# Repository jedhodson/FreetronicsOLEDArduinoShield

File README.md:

FreetronicsOLEDArduinoShield
============================

An Arduino shield for the Freetronics OLED Display

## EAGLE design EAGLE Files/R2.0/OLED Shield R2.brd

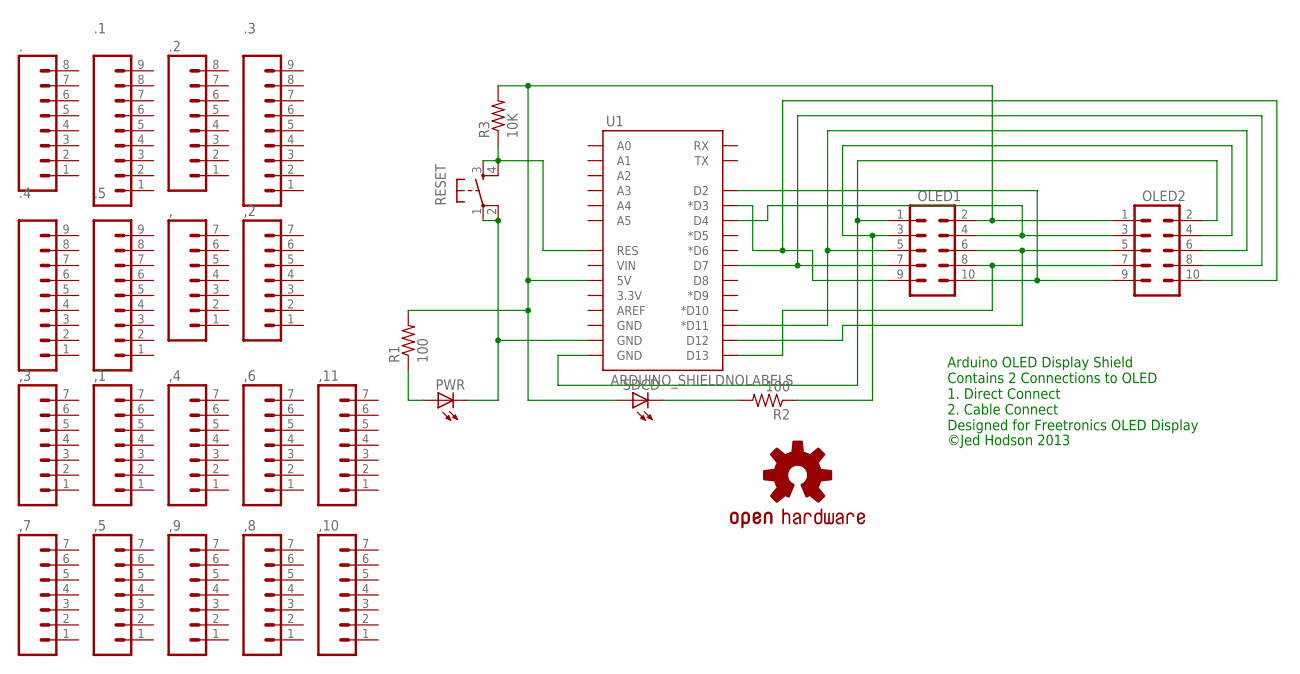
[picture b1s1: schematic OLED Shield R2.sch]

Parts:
,, ,1, ,2, ,3, ,4, ,5, ,6, ,7, ,8, ,9, ,10, ,11: M07; 1X07
., .2: M081X08; 1X08
.1, .3, .4, .5: M09; 1X09
LOGO1: OSHW-LOGOL; OSHW-LOGO-L
OLED1, OLED2: M05X2PTH; AVR_ICSP
PWR: LED5MM
R1, R2: 100; AXIAL-0.4
R3: 10K; AXIAL-0.4
RESET: TAC_SWITCHPTH; TACTILE-PTH
SDCD: LED5MM
U1: ARDUINO_SHIELDNOLABELS; DUEMILANOVE_SHIELD_NOLABELS

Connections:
GND: PWR.K (C), RESET.1, RESET.2, U1.GND@1 (GND)
unnamed: OLED1.2, OLED2.1, R1.P$2 (2), R3.P$2 (2), SDCD.A, U1.5V
unnamed: PWR.A, R1.P$1 (1)
unnamed: OLED1.10, OLED2.9, U1.D2
unnamed: OLED1.1, OLED2.2, U1.GND@0 (GND)
unnamed: OLED1.4, OLED2.3, U1.D4
unnamed: R2.P$2 (2), SDCD.K (C)
unnamed: OLED1.6, OLED2.5, U1.D12
unnamed: OLED1.5, OLED2.6, U1.D11 (*D11)
unnamed: OLED1.8, OLED2.7, U1.D13
unnamed: OLED1.7, OLED2.8, U1.D7
unnamed: R3.P$1 (1), RESET.3, RESET.4, U1.RES
unnamed: OLED1.3, OLED2.4, R2.P$1 (1)
unnamed: OLED1.9, OLED2.10, U1.D3 (*D3)

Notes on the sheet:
Arduino OLED Display Shield Contains 2 Connections to OLED 1. Direct Connect 2. Cable Connect Designed for Freetronics OLED Display
©Jed Hodson 2013

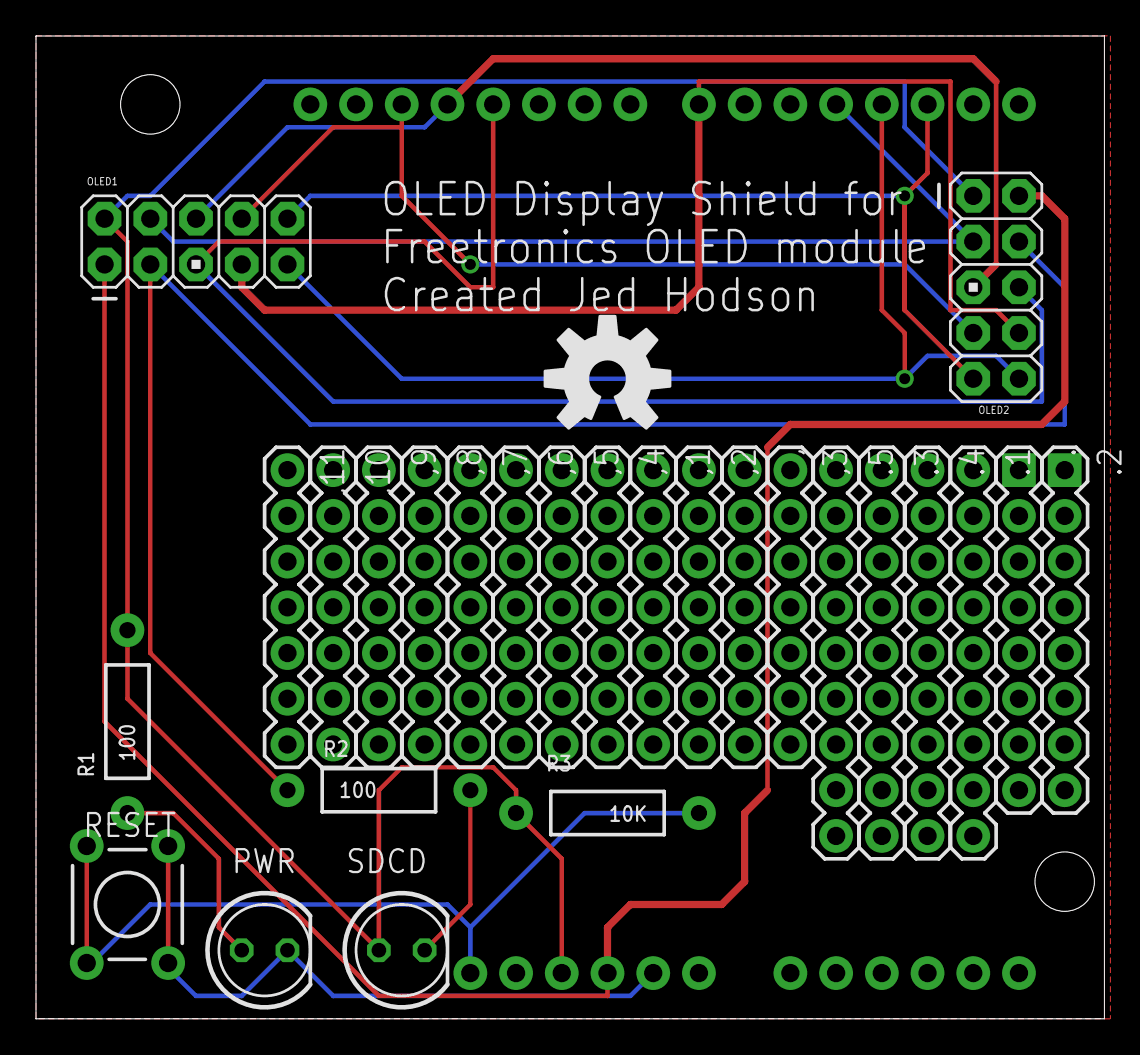
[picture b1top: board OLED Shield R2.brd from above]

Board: 2 copper layers, 59.4 x 54.6 mm, 28 parts (0 on the bottom side), 14 nets.

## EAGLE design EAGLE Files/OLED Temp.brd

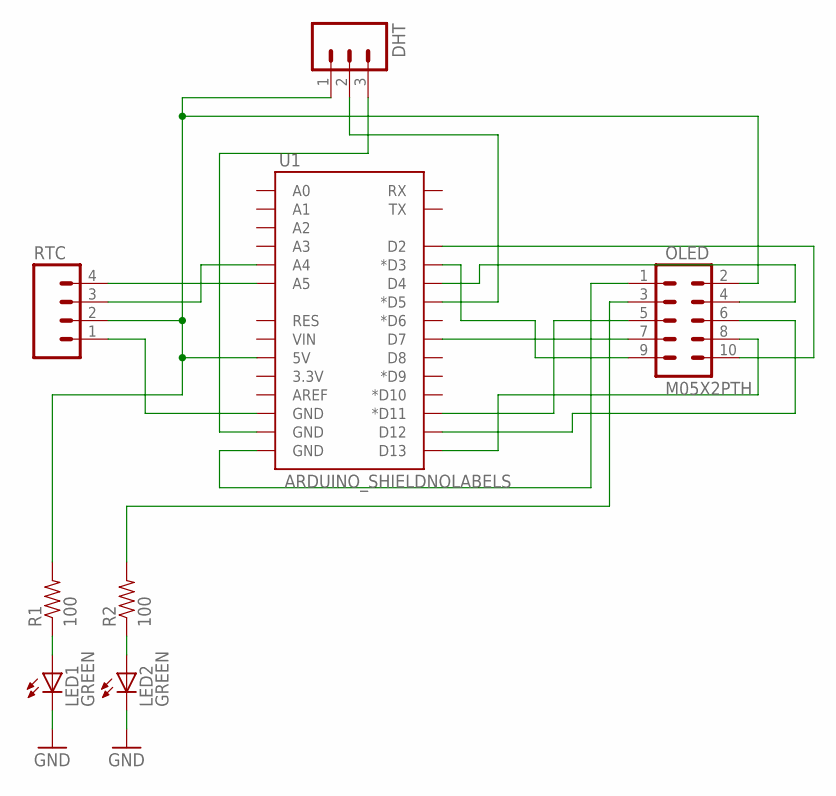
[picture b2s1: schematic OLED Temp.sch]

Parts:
DHT: SCREWTERMINAL-5MM-3
LED1, LED2: GREEN; LED5MM
OLED: M05X2PTH; AVR_ICSP
R1, R2: 100; AXIAL-0.4
RTC: 1X04
U1: ARDUINO_SHIELDNOLABELS; DUEMILANOVE_SHIELD_NOLABELS

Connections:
GND: LED1.K (C), LED2.K (C)
unnamed: DHT.1, OLED.2, R1.P$2 (2), RTC.2, U1.5V
unnamed: LED1.A, R1.P$1 (1)
unnamed: OLED.10, U1.D2
unnamed: OLED.1, U1.GND@0 (GND)
unnamed: OLED.4, U1.D4
unnamed: OLED.6, U1.D12
unnamed: OLED.5, U1.D11 (*D11)
unnamed: OLED.8, U1.D13
unnamed: OLED.7, U1.D7
unnamed: DHT.2, U1.D5 (*D5)
unnamed: DHT.3, U1.GND@1 (GND)
unnamed: RTC.1, U1.GND@2 (GND)
unnamed: RTC.3, U1.A4
unnamed: RTC.4, U1.A5
unnamed: LED2.A, R2.P$1 (1)
unnamed: OLED.3, R2.P$2 (2)
unnamed: OLED.9, U1.D3 (*D3)

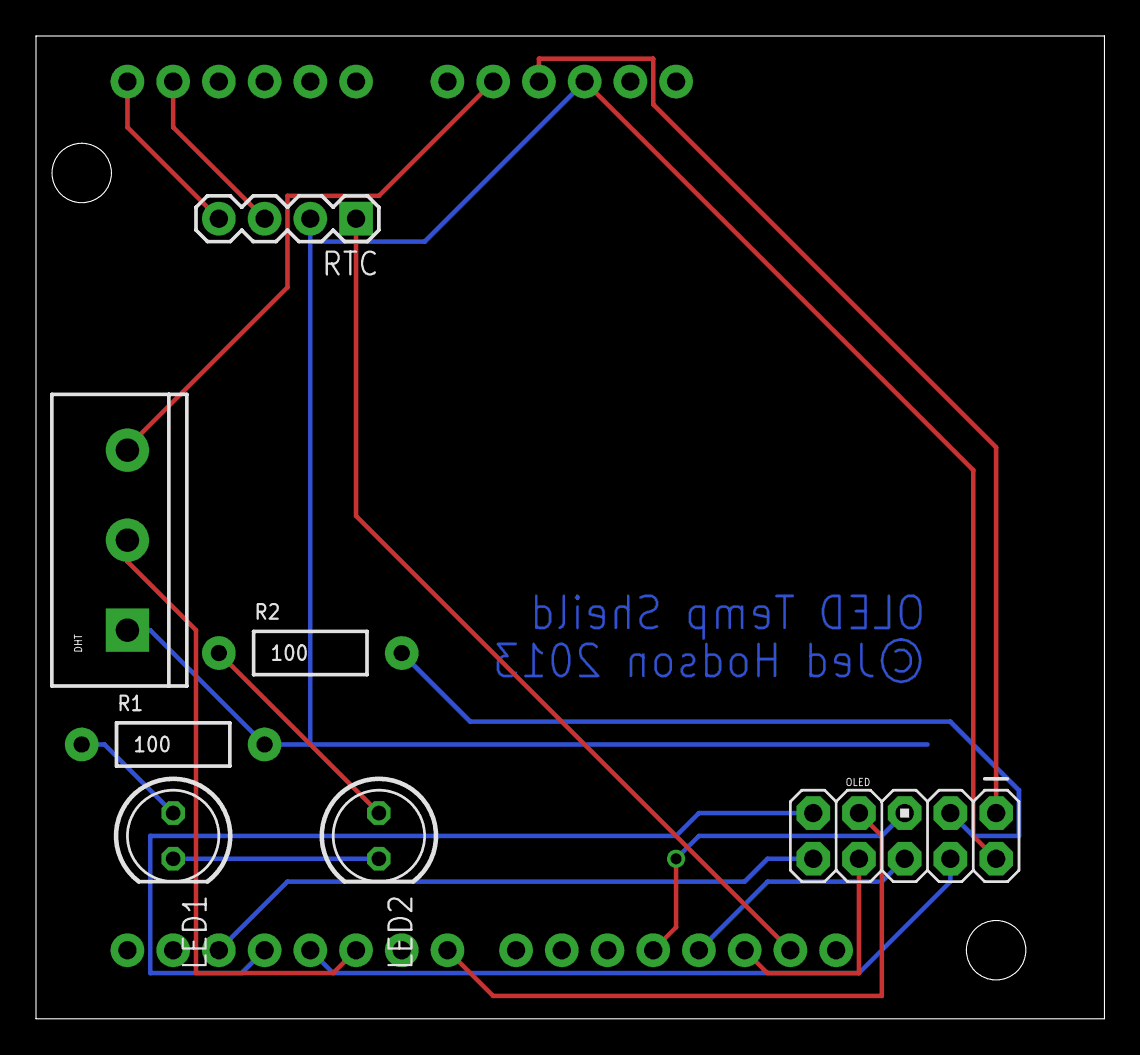
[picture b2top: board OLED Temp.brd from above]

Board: 2 copper layers, 59.4 x 54.6 mm, 8 parts (0 on the bottom side), 18 nets.

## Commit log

2013-09-23 EAGLE Files for Arduino shield
2013-09-23 Arduino example of temp and time on OLED
2013-09-23 git file
2013-09-25 EAGLE Files
2013-10-07 SKETCH UP FILES
2013-10-07 OLED Design Files
2013-10-16 RV2 of OLED Shield

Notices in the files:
parts and their libraries:
SparkFun-Boards: Licensing: CC v3.0 Share-Alike You are welcome to use this library for commercial purposes.
